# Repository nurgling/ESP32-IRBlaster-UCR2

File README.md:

# ESP32 IR blaster for the Unfolded Circle Remote Two.

This project implements the [Unfolded Circle Remote Two](https://www.unfoldedcircle.com/) dock API to add additional IR blasters
to your remote setup.

This allows the installation of an IR blaster in an independant location from where your
remote and charging dock are located. For example, in an equipment rack or cupboard, or for
multi-room setups.

## Requirements

1. An [Unfolded Circle Remote Two](https://www.unfoldedcircle.com/).
1. An supported ESP32 hardware (see Section [Supported Electronics](#supported-electronics))
1. [PlatformIO](https://platformio.org/) to build and upload firmware
1. Depending on used hardware: Some basic soldering / breadboarding skills and basic understanding of electronic.
1. Depending on used hardware: Some basic electronic parts and IR led.

## Getting Started

1. Clone project from Github and add to PlatformIO.
2. Select the build environment matching your dock hardware.
    - Add your specific board to ``platformio.ini``. Feel free to contribute this back as a pull-request.
3. If required, modify pin mappings in ``lib/config/blaster_config.h``, or by setting `-D defines` in the ``build_flags`` section of your build environment in ``platformio.ini``, respectively (see section [Customizing Pinout/Configuration](#customizing-pinout-configuration)).
    -  For enabling the *learning of IR codes* make sure you have added ``-DBLASTER_ENABLE_IR_LEARN=true`` to the build_flags of your used PlatformIO environment (or in blaster_config.h) and check the assigned GPIO pin.
    -  **Note:** IR learning feature is still under development and tested only with some basic IR codes.
4. Build *firmware* and *filesystem image* via PlattformIO actions for your target hardware.
5. Upload *firmware* and *filesystem image* to your ESP32 hardware (**Hint:** make sure no serial monitor is active during filesystem upload, otherwise upload will fail!).
    -  Details about SPIFFS filesystem image can be found in the respective [Section](#spiffs-filesystem-image)
6. Start discovering process on your Remote Two. The dock should be detected.
7. Perform setup process for dock via Remote Two.
8. Check serial logging for debugging.

⚠️ Do not forget to select the dock as "IR output device" in the configuration of your remotes!

## Customizing Pinout/Configuration 

The following defines are available in ``lib/config/blaster_config.h`` and can be overwritten by setting ``build_flags`` in ``platformio.ini``.

| Define | Description | Options |
|:-------|:------------|:--------|
|`BLASTER_INDICATOR_MODE` | Defines the type of indicator led used for custom dock | `INDICATOR_OFF` no indicator led available<br/>`INDICATOR_LED` single color led (__default__)<br/>`INDICATOR_PIXEL` digital RGB neopixel led |
|`BLASTER_PIN_INDICATOR` | Defines GPIO pin where indicator led is connected to  | Default: `5`<br/>Has no effect if `BLASTER_INDICATOR_MODE=INDICATOR_OFF` |
|`BLASTER_ENABLE_IR_INTERNAL` | Enables/Disables internal IR channel of dock | `true` channel is enabled (__default__)<br/> `false` channel is disabled |
|`BLASTER_PIN_IR_INTERNAL` | Defines GPIO pin of internal IR channel | Default: `12`<br/>Has no effect if `BLASTER_ENABLE_IR_INTERNAL=false` |
|`BLASTER_ENABLE_IR_OUT_1` | Enables/Disables external IR channel 1 of dock | `true` channel is enabled (__default__)<br/> `false` channel is disabled |
|`BLASTER_PIN_IR_OUT_1` | Defines GPIO pin of external IR channel 1 | Default: `13`<br/>Has no effect if `BLASTER_ENABLE_IR_OUT_1=false` |
|`BLASTER_ENABLE_IR_OUT_2` | Enables/Disables external IR channel 2 of dock | `true` channel is enabled (__default__)<br/> `false` channel is disabled |
|`BLASTER_PIN_IR_OUT_2` | Defines GPIO pin of external IR channel 2 | Default: `14`<br/>Has no effect if `BLASTER_ENABLE_IR_OUT_2=false` |
|`BLASTER_ENABLE_IR_LEARN` | Enables/Disables learning of IR codes by an IR receiver | `true` learning is enabled<br/> `false` learning is disabled  (__default__)|
|`BLASTER_PIN_IR_LEARN` | Defines GPIO pin IR receiver is connected to | Default: `16`<br/>Has no effect if `BLASTER_ENABLE_IR_LEARN=false` |
|`BLASTER_ENABLE_ETH` | Enables/Disables an wired Ethernet interface<br/>Currently only Olimex Boards supported. | `true` Ethernet interface available. Requires definition of `OLIMEX_ESP`<br/> `false` Ethernet interface not available  (__default__)|
|`OLIMEX_ESP` | Defines ESP32 package used in Olimex POE Board<br/>Impacts the pins for ethernet interface | `WROOM` tested and confirmed working<br/>`WROVER` untested ⚠️, therefore breaks build on purpose. Adaption in `eth_service.cpp` required!<br/>Has no effect if `BLASTER_ENABLE_ETH=false` |
|`BLASTER_ENABLE_OTA` | Enables Arduino OTA flashing.<br/>**Note**: This OTA function has nothing to do with firmware updates via Remote Two! | `true` OTA flashing is enabled <br/>`false` OTA flashing is not enabled (__default__)| 

## SPIFFS Filesystem Image

For providing details about the dock via a web user interface, files stored in an SPIFF file system are used.
The actual content of the SPIFFS filesystem image is the `data` directory of the project.

`data/spiffs_manifest.json` holds an index about all available files and their expected MD5 sums.
During boot, the dock will check availability of all files listed in the index and validate their checksum.

⚠️ Currently, the `fs_service` will only allow access to files mentioned in the index and available in the filesystem image, irrespecive of the checksum validataion. This might change in future.

**Hint:** In `tools/update_spiffs_manifest.py` a Python script is available to update the contents and MD5-checksums of the filesystem image index. Make sure the script is executed from the project's main folder.

# Supported Electronics

## KoeBlaster Hardware

*KoeBlaster* is designed to be a drop-in replacement of the Logitech Harmony Hub PCB working with Remote Two.

Schematic is tested and working. Comments are of course appreciated!

PCB is manufactured and working. 

[Manufacturing Data](kicad/KoeBlaster/exports) is available in the repository.

⚠️ When manufacturing, make sure you are using a **PCB height of 1mm**, as otherwise the mounting inside the Harmony Hub are not fitting. ⚠️

### Change History

| Revision | Changes | Known-Issues | 
|:-------|:------------|:------------|
| 0.2 | fixes of hw problems from v0.1 | none (yet) |
| 0.1 | initial design | value of current limitation resistors for IR leds too high.<br/>short-circuits on external blaster sockets.<br/>CH340 outputs voltages higher than 3.3V, therefore problems with hardware reset circuit. |

### Schematic

### Board

#### Top

#### Bottom

## Olimex ESP32-PoE-ISO + MOD-IRDA

Olimex offers some nice modules for people wanting Plug&Play solutions. 
Using the PlattformIO Environment `env:olimex_poe_iso` the pins shall already be pre-configured correctly for use with the MOD-IRDA extension board.

⚠️ From Olimex two IRDA add-ons are available (MOD-IRDA and MOD-IRDA+). Only MOD-IRDA is supported by this project! Due to different interfacing MOD-IRDA+ add-on is not compatible! ⚠️

### Customizing the pinout 

If you need to change the pinout feel free to do so. Here are the pins configured for the Olimex Board per default:

| Setting | Description |
|:-------|:------------|
|`BLASTER_INDICATOR_MODE` = `INDICATOR_OFF` | Olimex Board does not offer a led for custom usage, therfore indicator is turned off | 
|`BLASTER_ENABLE_IR_INTERNAL` = `true` | Enables internal IR channel of dock used by MOD-IRDA add-on |
|`BLASTER_PIN_IR_INTERNAL` = `4` | GPIO 4 is wired to UEXT header and used by IR sender on MOD-IRDA add-on |
|`BLASTER_ENABLE_IR_OUT_1` = `false` | Disables external IR channel 1 of dock by default. <br/>If you plan to add external circuity set to `true` and configure `BLASTER_PIN_IR_OUT_1` accordingly (only `GPIO0-31` are supproted) |
|`BLASTER_ENABLE_IR_OUT_2` = `false` | Disables external IR channel 2 of dock by default. <br/>If you plan to add external circuity set to `true` and configure `BLASTER_PIN_IR_OUT_2` accordingly (only `GPIO0-31` are supproted) |
|`BLASTER_ENABLE_IR_LEARN` = `true`  | Enables learning of IR codes by an IR receiver | 
|`BLASTER_PIN_IR_LEARN` = `36` | GPIO 36 is wired to UEXT header and used by IR receiver on MOD-IRDA add-on |
|`BLASTER_ENABLE_ETH` = `true` | Enables the wired Ethernet interface of Olimex board | 
|`OLIMEX_ESP` = `WROOM` | Defines ESP32 package used in Olimex POE Board. Currently only `WROOM` is tested and confirmed working<br/>`WROVER` untested ⚠️, therefore breaks build on purpose. Adaption in `eth_service.cpp` required!<br/>Has no effect if `BLASTER_ENABLE_ETH=false` |

### Links to Olimex product pages

[Olimex PoE Iso Board](https://www.olimex.com/Products/IoT/ESP32/ESP32-POE-ISO/open-source-hardware)

[Olimex MOD-IRDA](https://www.olimex.com/Products/Modules/Interface/MOD-IRDA/open-source-hardware)

## DIY Breadboard Example

At least one IR led + transistors and resistors is required for this to operate correctly.
IR learning was tested with an CHQ1838 Infrared receiver module.

Schematic (⚠️ needs update for IR learning!):

# Integrating with the remote

In the remote web interface:

1. Select *Integrations & docks*
1. Under *Docks* click *+*
1. Click on *Discover Docks*
1. Dock should be recognized either via Bluetooth or via WiFi/Ethernet
1. If recognized via Bluetooth, you have to mandatorily specify Wifi settings during adoption process.
1. Click *Next*
1. The blaster should be added as a new dock. If there were issues, then download the recent log files in
*Settings* / *Development* / *Logs*. There should be a reason for any failures logged by the remote.
1. For debugging, the blaster also provides extensive logging output via the serial interface.

# Caveats

The Unfolded Circle Remote Two API, while [documented](https://github.com/unfoldedcircle/core-api/blob/main/dock-api/README.md),
the API could change with a remote update before this library is updated. 

This project is not from Unfolded Circle, so do not ask for support there.

This is just a minimal implementation, and doesn't not support OTA updates, web config, etc at this stage.

The Unfolded Circle web interface will report an error when attempting to check for firmware updates. This is normal as
the remote does not know about this particular dock.

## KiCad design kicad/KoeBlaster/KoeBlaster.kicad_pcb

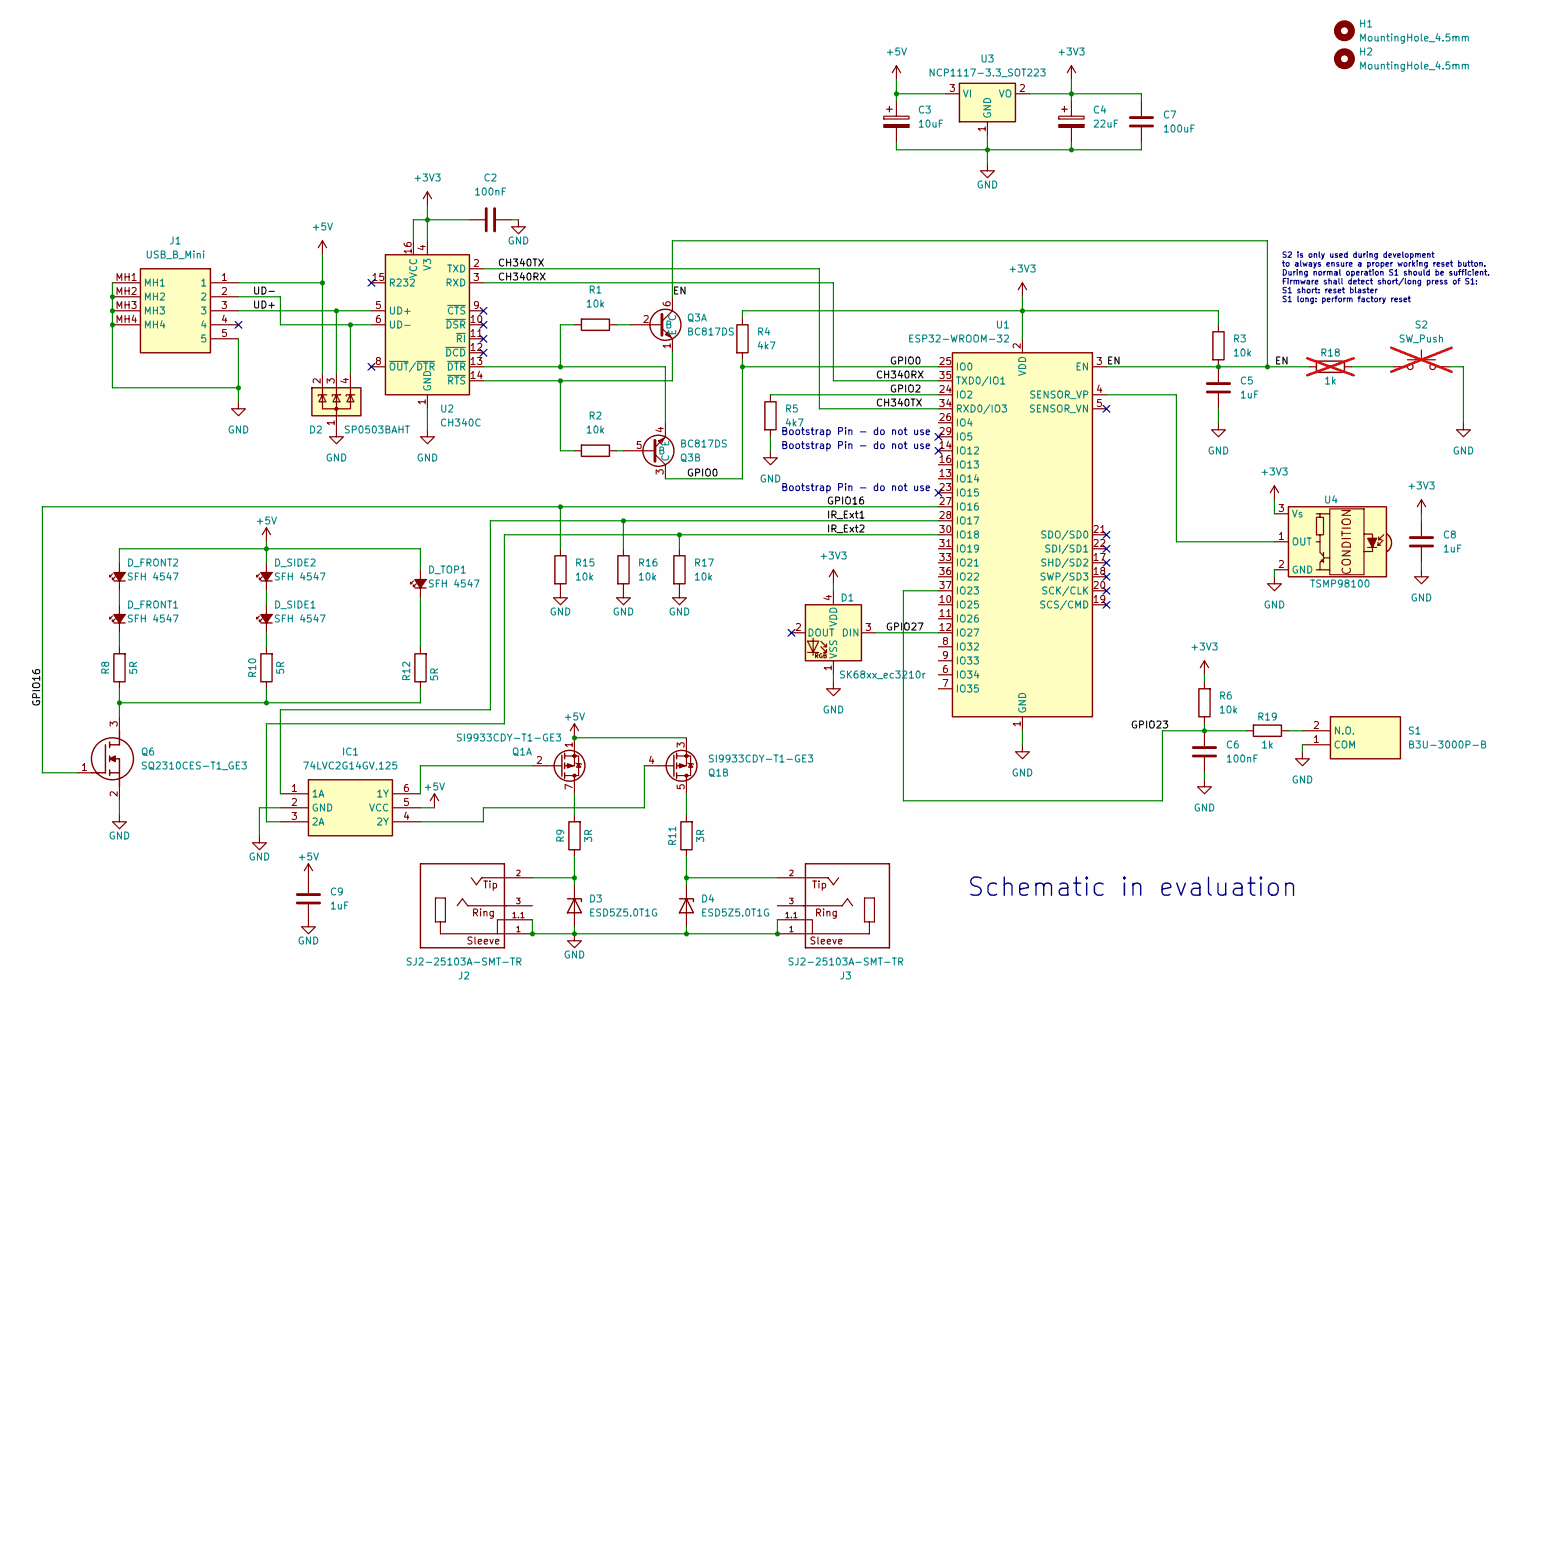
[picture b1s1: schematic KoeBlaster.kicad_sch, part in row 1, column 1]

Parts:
C2, C6: 100nF; C_0805_2012Metric_Pad1.18x1.45mm_HandSolder
C3: 10uF; CP_EIA-2012-15_AVX-P_Pad1.30x1.05mm_HandSolder
C4: 22uF; CP_EIA-2012-15_AVX-P_Pad1.30x1.05mm_HandSolder
C5, C8, C9: 1uF; C_0805_2012Metric_Pad1.18x1.45mm_HandSolder
C7: 100uF; C_0805_2012Metric_Pad1.18x1.45mm_HandSolder
D1: SK68xx_ec3210r; SK68xx-EC3210R
D2: SP0503BAHT; SOT-143
D3, D4: ESD5Z5.0T1G; D_SOD-523
D_FRONT1, D_FRONT2: SFH 4547; LED_D5.0mm_Horizontal_O6.35mm_Z3.0mm
D_SIDE1, D_SIDE2: SFH 4547; LED_D5.0mm_Horizontal_O3.81mm_Z3.0mm
D_TOP1: SFH 4547; LED_D5.0mm_IRBlack
H1, H2: MountingHole_4.5mm
IC1: 74LVC2G14GV,125; SOT95P275X110-6N; Mouser Part Number 771-LVC2G14GV125
J1: USB_B_Mini; 629105150521; Mouser Part Number 710-629105150521
J2, J3: SJ2-25103A-SMT-TR; CUI_SJ2-25103A-SMT-TR; PARTREV 1.01
Q1: SI9933CDY-T1-GE3; SOIC-8_3.9x4.9mm_P1.27mm
Q3: BC817DS; SOT95P275X110-6N; Mouser Part Number 771-BC817DSF
Q6: SQ2310CES-T1_GE3; SOT95P237X112-3N; Manufacturer_Part_Number SQ2310CES-T1_GE3
R1, R2, R3, R6, R15, R16, R17: 10k; R_0805_2012Metric_Pad1.20x1.40mm_HandSolder
R4, R5: 4k7; R_0805_2012Metric_Pad1.20x1.40mm_HandSolder
R8, R10, R12: 5R; R_0805_2012Metric_Pad1.20x1.40mm_HandSolder
R9, R11: 3R; R_0805_2012Metric_Pad1.20x1.40mm_HandSolder
R18: 1k; R_0805_2012Metric_Pad1.20x1.40mm_HandSolder; not fitted
R19: 1k; R_0805_2012Metric_Pad1.20x1.40mm_HandSolder
S1: B3U-3000P-B; B3U3000PB; Mouser Part Number 653-B3U-3000P-B
S2: SW_Push; SW_SPST_B3U-1000P; not fitted
U1: ESP32-WROOM-32
U2: CH340C; SOIC-16_3.9x9.9mm_P1.27mm
U3: NCP1117-3.3_SOT223; SOT-223-3_TabPin2
U4: TSMP98100; Vishay_MINICAST-3Pin

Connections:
+3V3: C2.1, C4.1, C7.1, C8.1, D1.4 (VDD), R3.1, R4.1, R6.2, U1.2 (VDD), U2.4 (V3), U2.16 (VCC), U3.2 (VO), U4.3 (Vs)
+5V: C3.1, C9.1, D2.2 (K), D_FRONT2.2 (A), D_SIDE2.2 (A), D_TOP1.2 (A), IC1.5 (VCC), J1.1, Q1.1 (S1), Q1.3 (S2), U3.3 (VI)
/CH340RX: U1.35 (TXD0/IO1), U2.3 (RXD)
/CH340TX: U1.34 (RXD0/IO3), U2.2 (TXD)
/EN: C5.1, Q3.6 (C), R3.2, R18.2, U1.3 (EN)
/GPIO0: Q3.3 (C), R4.2, U1.25 (IO0)
/GPIO2: R5.1, U1.24 (IO2)
/GPIO16: Q6.1 (G), R15.1, U1.27 (IO16)
/GPIO23: C6.1, R6.1, R19.2, U1.37 (IO23)
/GPIO27: D1.3 (DIN), U1.12 (IO27)
/IR_Ext1: IC1.1 (1A), R16.1, U1.28 (IO17)
/IR_Ext2: IC1.3 (2A), R17.1, U1.30 (IO18)
/UD+: D2.3 (K), J1.3, U2.5 (UD+)
/UD-: D2.4 (K), J1.2, U2.6 (UD-)
GND: C2.2, C3.2, C4.2, C5.2, C6.2, C7.2, C8.2, C9.2, D1.1 (VSS), D2.1 (A), D3.2 (A), D4.2 (A), IC1.2 (GND), J1.5, J1.MH1, J1.MH2, J1.MH3, J1.MH4, J2.1, J2.1.1, J3.1, J3.1.1, Q6.2 (S), R5.2, R15.2, R16.2, R17.2, S1.1 (COM), S2.2, U1.1 (GND), U1.15 (GND), U1.38 (GND), U1.39 (GND), U2.1 (GND), U3.1 (GND), U4.2 (GND)
unnamed: D3.1 (K), J2.2, R9.1
unnamed: D4.1 (K), J3.2, R11.1
unnamed: D_FRONT1.2 (A), D_FRONT2.1 (K)
unnamed: D_FRONT1.1 (K), R8.2
unnamed: D_SIDE1.2 (A), D_SIDE2.1 (K)
unnamed: D_SIDE1.1 (K), R10.2
unnamed: D_TOP1.1 (K), R12.2
unnamed: IC1.6 (1Y), Q1.2 (G1)
unnamed: IC1.4 (2Y), Q1.4 (G2)
unnamed: Q1.7 (D1), Q1.8 (D1), R9.2
unnamed: Q1.5 (D2), Q1.6 (D2), R11.2
unnamed: Q3.2 (B), R1.1
unnamed: Q3.1 (E), R2.2, U2.14 (~RTS)
unnamed: Q3.5 (B), R2.1
unnamed: Q3.4 (E), R1.2, U2.13 (~DTR)
unnamed: Q6.3 (D), R8.1, R10.1, R12.1
unnamed: R18.1, S2.1
unnamed: R19.1, S1.2 (N.O.)
unnamed: U1.4 (SENSOR_VP), U4.1 (OUT)

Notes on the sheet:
S2 is only used during development to always ensure a proper working reset button. During normal operation S1 should be sufficient. Firmware shall detect short/long press of S1: S1 short: reset blaster S1 long: perform factory reset
Bootstrap Pin - do not use
Schematic in evaluation

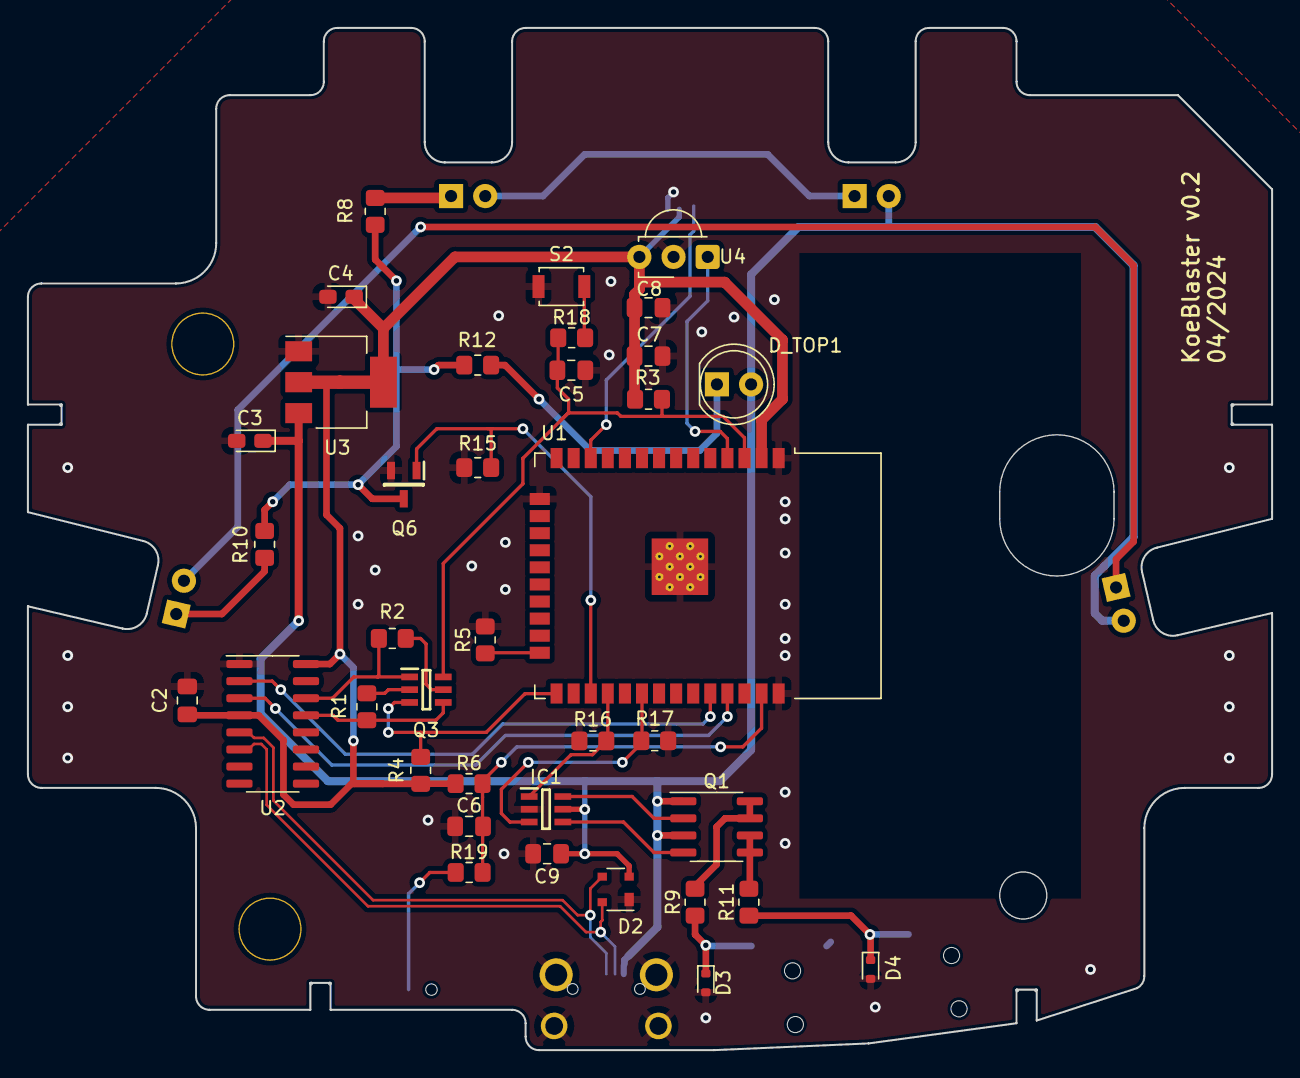
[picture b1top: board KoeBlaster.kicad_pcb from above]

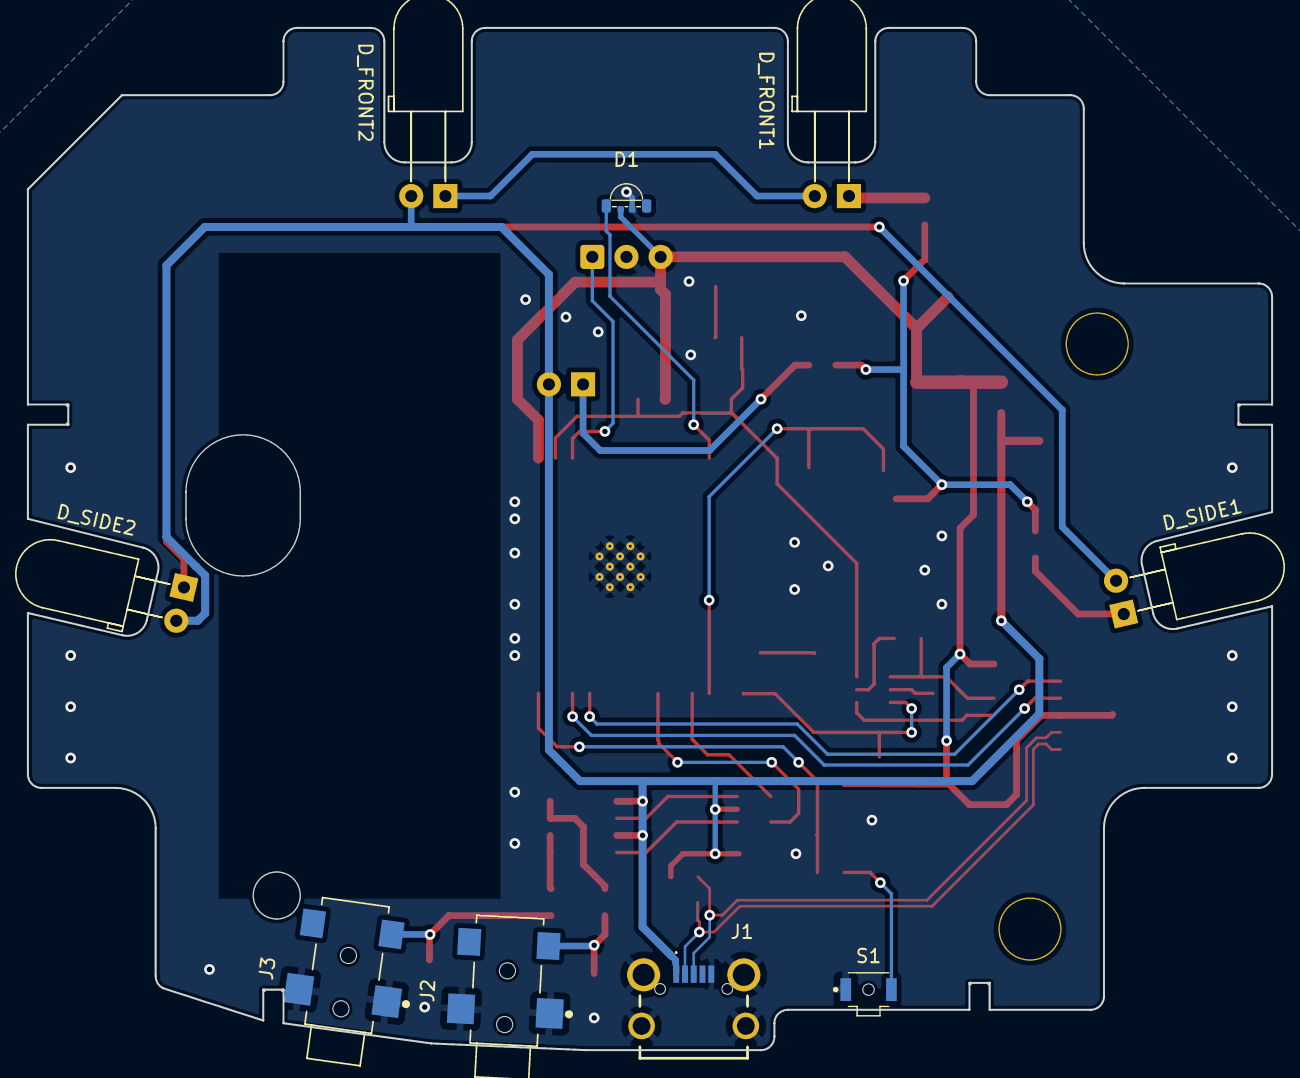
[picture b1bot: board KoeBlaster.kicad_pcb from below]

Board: 2 copper layers, 92.5 x 76.0 mm, 48 parts (9 on the bottom side), 34 nets.

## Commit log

2024-02-24 fixed problems with wrong ws fragmentation headers
2024-02-24 updated external libraries and fixed some static code check warnings
2024-02-24 add github build automation
2024-02-25 fixed some codeql findings
2024-02-28 - raise MAX_IR_CODE_LENGTH to 4096 - raise SOCKET_DATA_SIZE to 8192
2024-03-02 implemented learning of ir codes. switch to esp_log calls
2024-03-02 fixed pin collision of ir learning pin with original setup
2024-03-02 Update README.md
    Added info about IR learning
2024-03-03 small cleanup of includes
2024-03-16 Initial implementation of Ethernet Support
2024-03-17 Changed Olimex default pinout. Added available customization build flags to Readme.md
2024-03-27 Added KoeBlaster hardware; Draft schematic and initial version of pcb board
2024-03-29 various improvements on schematic and pcb
2024-03-30 prepare everything for hw revision 0.1
2024-04-05 pixel indicator led support working
2024-04-07 add sw reset button and simple status web page
2024-04-08 fixed buildbreak if no sw reset button is available
2024-04-18 add dock uptime and logo to status page
2024-04-18 add ota support
2024-04-25 updated pcb to v0.2
2024-04-27 update the http dock status page
2024-05-05 reworked spiffs handling and web frontend
2024-05-05 change default breath to green and start breathing immediately
2024-05-08 update wifi state and led indication. encapsulation of unavailable eth
2024-05-26 Documentation of readme.md and handling of missing filesystem in web task
2024-05-26 Reworking LED Output
